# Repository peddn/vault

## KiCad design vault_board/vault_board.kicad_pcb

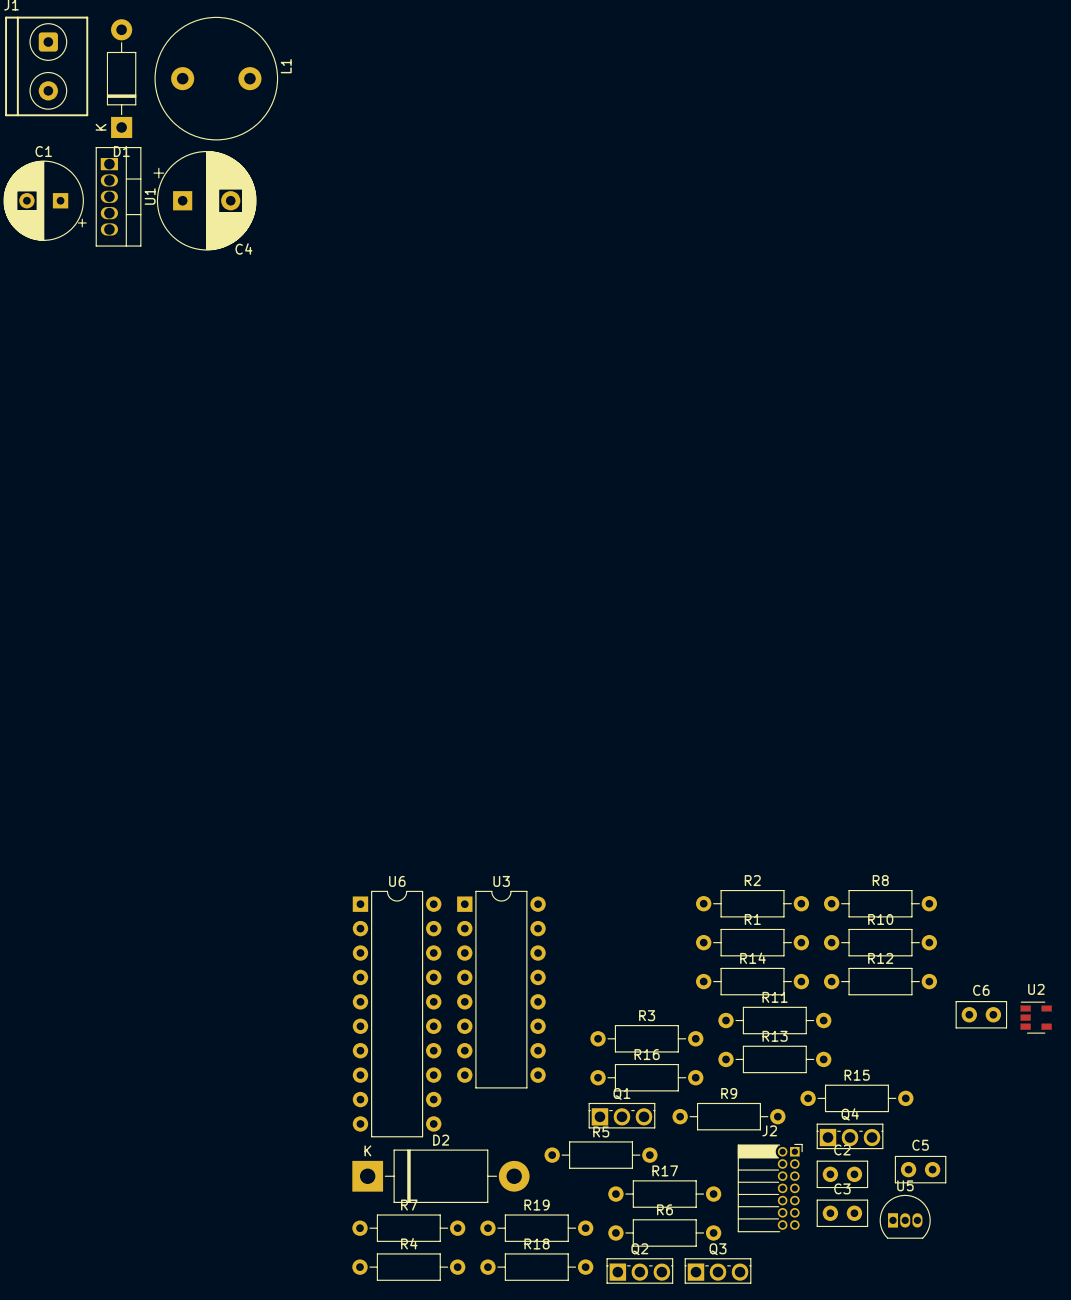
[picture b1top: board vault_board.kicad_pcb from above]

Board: 2 copper layers, 39 parts (0 on the bottom side), 40 nets, no tracks yet.

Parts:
C1: 100u; CP_Radial_D8.0mm_P3.50mm
C2, C3, C5, C6: 0.1u; C_Disc_D5.0mm_W2.5mm_P2.50mm
C4: 330u; CP_Radial_D10.0mm_P5.00mm
D1: 1N5819; D_DO-41_SOD81_P10.16mm_Horizontal
D2: 1N5400; D_DO-201AD_P15.24mm_Horizontal
J1: Jack-DC; Terminal_1x2_508_RND
J2: Conn_01x11; PinSocket_2x07_P1.27mm_Horizontal
L1: 330u; L_Radial_D12.5mm_P7.00mm_Fastron_09HCP
Q1, Q2, Q3: IRFU5505PBF; TO-251-3_Vertical
Q4: IRFU024NPBF; TO-251-3_Vertical
R1, R2, R4, R14: 10k; R_Axial_DIN0207_L6.3mm_D2.5mm_P10.16mm_Horizontal
R3, R17: 1k; R_Axial_DIN0207_L6.3mm_D2.5mm_P10.16mm_Horizontal
R5, R15, R16, R18, R19: R; R_Axial_DIN0207_L6.3mm_D2.5mm_P10.16mm_Horizontal
R6, R7, R8, R9, R10, R11, R12, R13: 560; R_Axial_DIN0207_L6.3mm_D2.5mm_P10.16mm_Horizontal
U1: LM2575T-5G; TO-220-5_Vertical
U2: 74LVC1G14; SOT-23-5
U3: TPIC6C595; DIP-16_W7.62mm
U5: DS1233; TO-92_Inline
U6: ATtiny861-20PU; DIP-20_W7.62mm

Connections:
+5V: C3.2, C4.1, C5.2, C6.2, L1.2, R1.1, R2.1, R4.1, R5.1, R14.1, R15.1, R16.1, U1.4, U2.5, U3.1, U5.3, U6.5, U6.15
+12V: C1.1, D2.1, J1.1, Q1.3, Q2.3, Q3.3, U1.1
D1: R17.2, U6.20
D2: R18.2, U6.19
D3: R19.2, U6.18
ENC_A: R1.2, U6.13
ENC_B: R2.2, U6.12
ENC_S: U2.4, U6.11
GND: C1.2, C2.2, C3.1, C4.2, C5.1, C6.1, D1.2, J1.2, Q4.3, U1.3, U1.5, U2.3, U3.16, U5.1, U6.6, U6.16
unnamed: C2.1, R3.1, R4.2, U2.2
unnamed: D1.1, L1.1, U1.2
unnamed: D2.2, Q4.2
unnamed: J2.1, R6.1
unnamed: J2.2, R7.1
unnamed: J2.3, R8.1
unnamed: J2.4, R9.1
unnamed: J2.5, R10.1
unnamed: J2.6, R11.1
unnamed: J2.7, R12.1
unnamed: J2.8, R13.1
unnamed: J2.9, Q3.2
unnamed: J2.10, Q2.2
unnamed: J2.11, Q1.2
unnamed: Q1.1, R14.2, R17.1
unnamed: Q2.1, R15.2, R18.1
unnamed: Q3.1, R16.2, R19.1
unnamed: R5.2, U3.7
unnamed: R6.2, U3.3
unnamed: R7.2, U3.4
unnamed: R8.2, U3.5
unnamed: R9.2, U3.6
unnamed: R10.2, U3.11
unnamed: R11.2, U3.12
unnamed: R12.2, U3.13
unnamed: R13.2, U3.14
RCK: U3.10, U6.3
SER_IN: U3.2, U6.1
SRCK: U3.15, U6.2
~G: U3.8, U6.4
~RESET: U5.2, U6.10
